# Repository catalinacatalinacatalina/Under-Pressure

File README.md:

# Under Pressure - Analog Distortion Pedal

A complete documentation of designing and building an analog distortion pedal for electric guitars, based on Brian Wampler's minimal parts-count circuit design.

### 🎵 About the Name

**Under Pressure** is named after the iconic 1981 song by David Bowie & Queen. The name captures the essence of what a distortion pedal does: it takes the natural dynamics of a guitar signal and compresses it under intense pressure, forcing it through clipping stages that create the characteristic aggressive and driven tone.

## 🎯 Project Overview

This project is divided into **three distinct phases**, each with its own workflow and deliverables:

1. **Phase 01: Breadboard Prototype** - Testing and validation on solderless breadboard
2. **Phase 02: PCB Design** - Professional PCB layout and manufacturing
3. **Phase 03: PCB Soldering** - Attaching the components to the designed PCB

## ✅ Current Build Status

- **Breadboard Prototype**: Complete and working with guitar + amp validation.
- **PCB Design**: Complete (layout, DRC, Gerbers, and drill files generated).
- **Manufacturer Order**: Pending submission.

## 📐 Circuit Architecture

- ⚡ **Stage 1**: 9V battery with virtual ground (Vref) biasing
- 📈 **Stage 2**: implements two gain stages with clipping diodes to shape the distortion character
- 🎚️ **Stage 3**: provides final amplification with impedance buffering for clean output

## 📂 Project Structure

```
├── docs/              # Design documentation & notes
├── hardware/          # Circuit & PCB files
│   ├── breadboard/    # Phase 01: Prototype testing
│   ├── components/    # Datasheets & BOM
│   ├── pcb/           # Phase 02: PCB design & Gerber files
│   └── schematics/    # KiCad schematics
├── simulations/       # SPICE circuit analysis
├── audio/             # Test recordings
└── images/            # Build photos & diagrams
```

## 🚀 Quick Start

### For Breadboard (Phase 01)

1. Understand the schematics
2. Buy the needed components
3. Replicate the circuit on a breadboard
4. Plug your guitar, test audio and tone
5. Confirm ready for PCB

### For PCB Design (Phase 02)

1. Use KiCad (9.0) to create schematics
2. Design PCB layout
3. Generate Gerber files
4. Run final DRC/ERC checks
5. Place order with PCB manufacturer

### For PCB Soldering (Phase 03)
...

## 📚 Documentation Roadmap

```
PHASE 01: Breadboard                    PHASE 02: PCB Design                    PHASE 03: PCB Soldering
├── ✅ Understand circuit               ├── ✅ Verify breadboard values         ├── ⏳ Prepare soldering tools
├── ✅ Source components                ├── ✅ Create schematic in KiCad        ├── ⏳ Solder components
├── ✅ Build on breadboard              ├── ✅ Design PCB layout                ├── ⏳ Inspect solder joints
├── ✅ Test audio and tone              ├── ✅ Run design rule check (DRC)      └── ⏳ Test PCB functionality
├── ✅ Document final values            ├── ✅ Generate Gerber files
└── ✅ Confirm ready for PCB            └── ⏳ Order PCB
```

## 🔗 References

- **Main Tutorial**: [How to Design a Basic Distortion Pedal Circuit](https://www.wamplerpedals.com/blog/lifestyle-hobby/2024/08/how-to-design-a-basic-distortion-pedal-circuit/) - Brian Wampler
- **Main Component Sourcing**: Electronica Embajadores - https://www.electronicaembajadores.com/es/

## 📊 Project Status

| Phase | Status | Progress |
|-------|--------|----------|
| Phase 01: Breadboard | ✅ Done | Fully working and validated |
| Phase 02: PCB Design | ✅ Done | Designed and ready for manufacturer order |
| Phase 03: PCB Soldering | ⏳ Pending | Waiting for manufactured PCB delivery |

## 🛠️ Tools Needed

**Phase 01 (Breadboard)**:
- Solderless breadboard
- Multimeter (for voltage/continuity testing)
- Wires
- Guitar & amplifier (for audio testing)

**Phase 02 (PCB Design)**:
- KiCad
- Gerber viewer (integrated in KiCad)
- PCB manufacturer (JLCPCB, PCBWay, Elecrow, etc.)

**Phase 03 (PCB Soldering)**:
- Soldering iron
- Lead-free solder (0.8-1.0mm)
- Solder sucker or desoldering wick
- Brass cleaner or damp sponge
- Helping hands tool

---

**Last Updated**: April 25, 2026 | **Design Based On**: Wampler Basic Distortion Circuit (Aug 2024) | **Build Status**: Breadboard complete, PCB designed, pending manufacturer order

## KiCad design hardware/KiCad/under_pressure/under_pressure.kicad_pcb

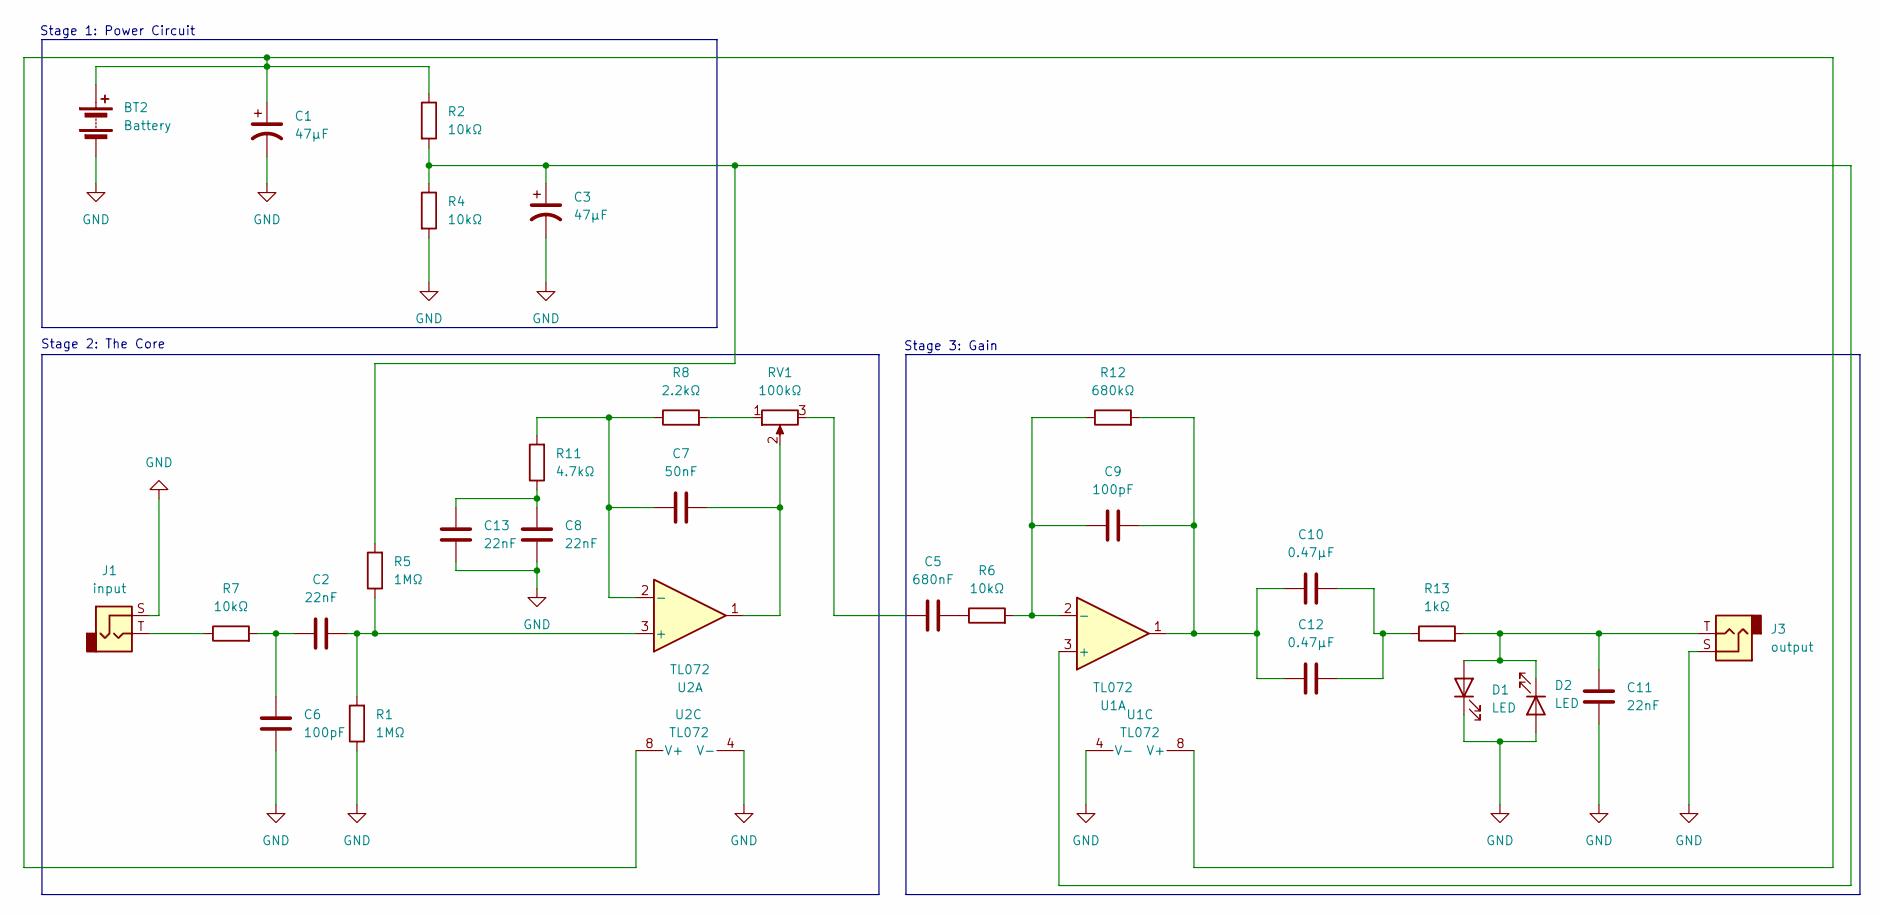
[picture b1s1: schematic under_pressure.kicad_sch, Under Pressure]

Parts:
BT2: Battery; SolderWire-0.1sqmm_1x02_P3.6mm_D0.4mm_OD1mm
C1, C3: 47µF; CP_Radial_D5.0mm_P2.50mm
C2, C8, C11, C13: 22nF; C_Disc_D3.0mm_W1.6mm_P2.50mm
C5: 680nF; C_Disc_D3.0mm_W1.6mm_P2.50mm
C6, C9: 100pF; C_Disc_D3.0mm_W1.6mm_P2.50mm
C7: 50nF; C_Disc_D3.0mm_W1.6mm_P2.50mm
C10, C12: 0.47µF; C_Disc_D3.0mm_W1.6mm_P2.50mm
D1, D2: LED; LED_D5.0mm
J1: input; SolderWire-0.1sqmm_1x02_P3.6mm_D0.4mm_OD1mm
J3: output; SolderWire-0.1sqmm_1x02_P3.6mm_D0.4mm_OD1mm
R1, R5: 1MΩ; R_Axial_DIN0207_L6.3mm_D2.5mm_P7.62mm_Horizontal
R2, R4, R6, R7: 10kΩ; R_Axial_DIN0207_L6.3mm_D2.5mm_P7.62mm_Horizontal
R8: 2.2kΩ; R_Axial_DIN0207_L6.3mm_D2.5mm_P7.62mm_Horizontal
R11: 4.7kΩ; R_Axial_DIN0207_L6.3mm_D2.5mm_P7.62mm_Horizontal
R12: 680kΩ; R_Axial_DIN0207_L6.3mm_D2.5mm_P7.62mm_Horizontal
R13: 1kΩ; R_Axial_DIN0207_L6.3mm_D2.5mm_P7.62mm_Horizontal
RV1: 100kΩ; Potentiometer_Alps_RK163_Single_Horizontal
U1: TL072
U2: TL072; DIP-8_W7.62mm

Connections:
GND: BT2.2 (-), C1.2, C3.2, C6.1, C8.2, C11.2, C13.2, D1.1 (K), D2.2 (A), J1.S, J3.S, R1.1, R4.2, U1.4 (V-), U2.4 (V-)
unnamed: BT2.1 (+), C1.1, R2.1, U1.8 (V+), U2.8 (V+)
unnamed: C2.1, C6.2, R7.2
unnamed: C5.1, RV1.3
unnamed: C5.2, R6.1
unnamed: C7.2, RV1.2, U2.1
unnamed: C9.2, C10.1, C12.1, R12.2, U1.1
unnamed: C10.2, C12.2, R13.1
unnamed: C8.1, C13.1, R11.1
unnamed: C11.1, D1.2 (A), D2.1 (K), J3.T, R13.2
unnamed: J1.T, R7.1
unnamed: R8.2, RV1.1
unnamed: C3.1, R2.2, R4.1, R5.2, U1.3 (+)
unnamed: C9.1, R6.2, R12.1, U1.2 (-)
unnamed: C2.2, R1.2, R5.1, U2.3 (+)
unnamed: C7.1, R8.1, R11.2, U2.2 (-)

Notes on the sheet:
Stage 2: The Core
Stage 3: Gain
Stage 1: Power Circuit

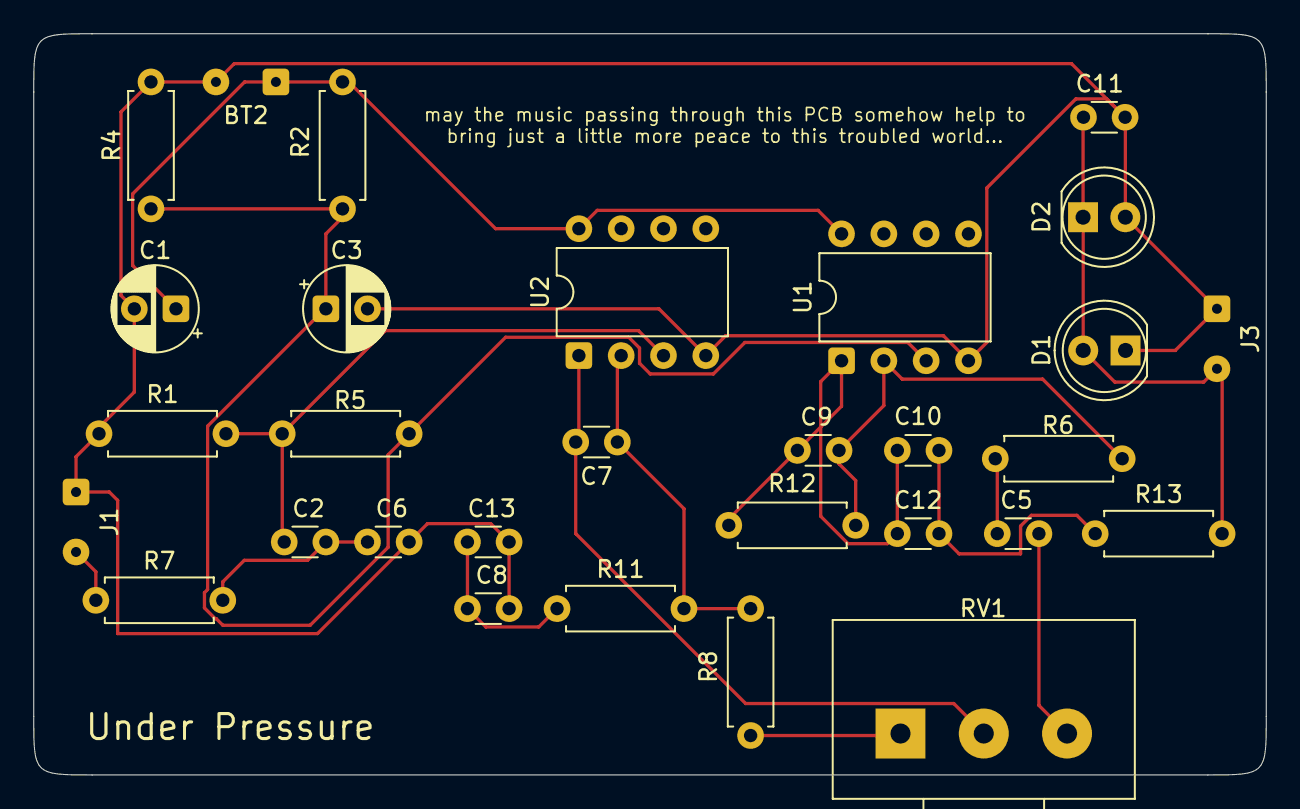
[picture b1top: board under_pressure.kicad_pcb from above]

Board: 2 copper layers, 74.0 x 44.5 mm, 30 parts (0 on the bottom side), 16 nets.

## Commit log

2026-04-07 design update
2026-04-07 Doc: Add PCB soldering phase and schematics
2026-04-09 Update hardware schematic images
2026-04-11 renaming
2026-04-16 Add project structure to README
2026-04-17 archivos kicad
2026-04-18 cableado + esquematico arreglado
2026-04-25 gerbers
2026-04-25 readmes
2026-04-25 Update docs about project current status
